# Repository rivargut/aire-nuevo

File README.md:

# aire-nuevo
Code for Aire Nuevo FW

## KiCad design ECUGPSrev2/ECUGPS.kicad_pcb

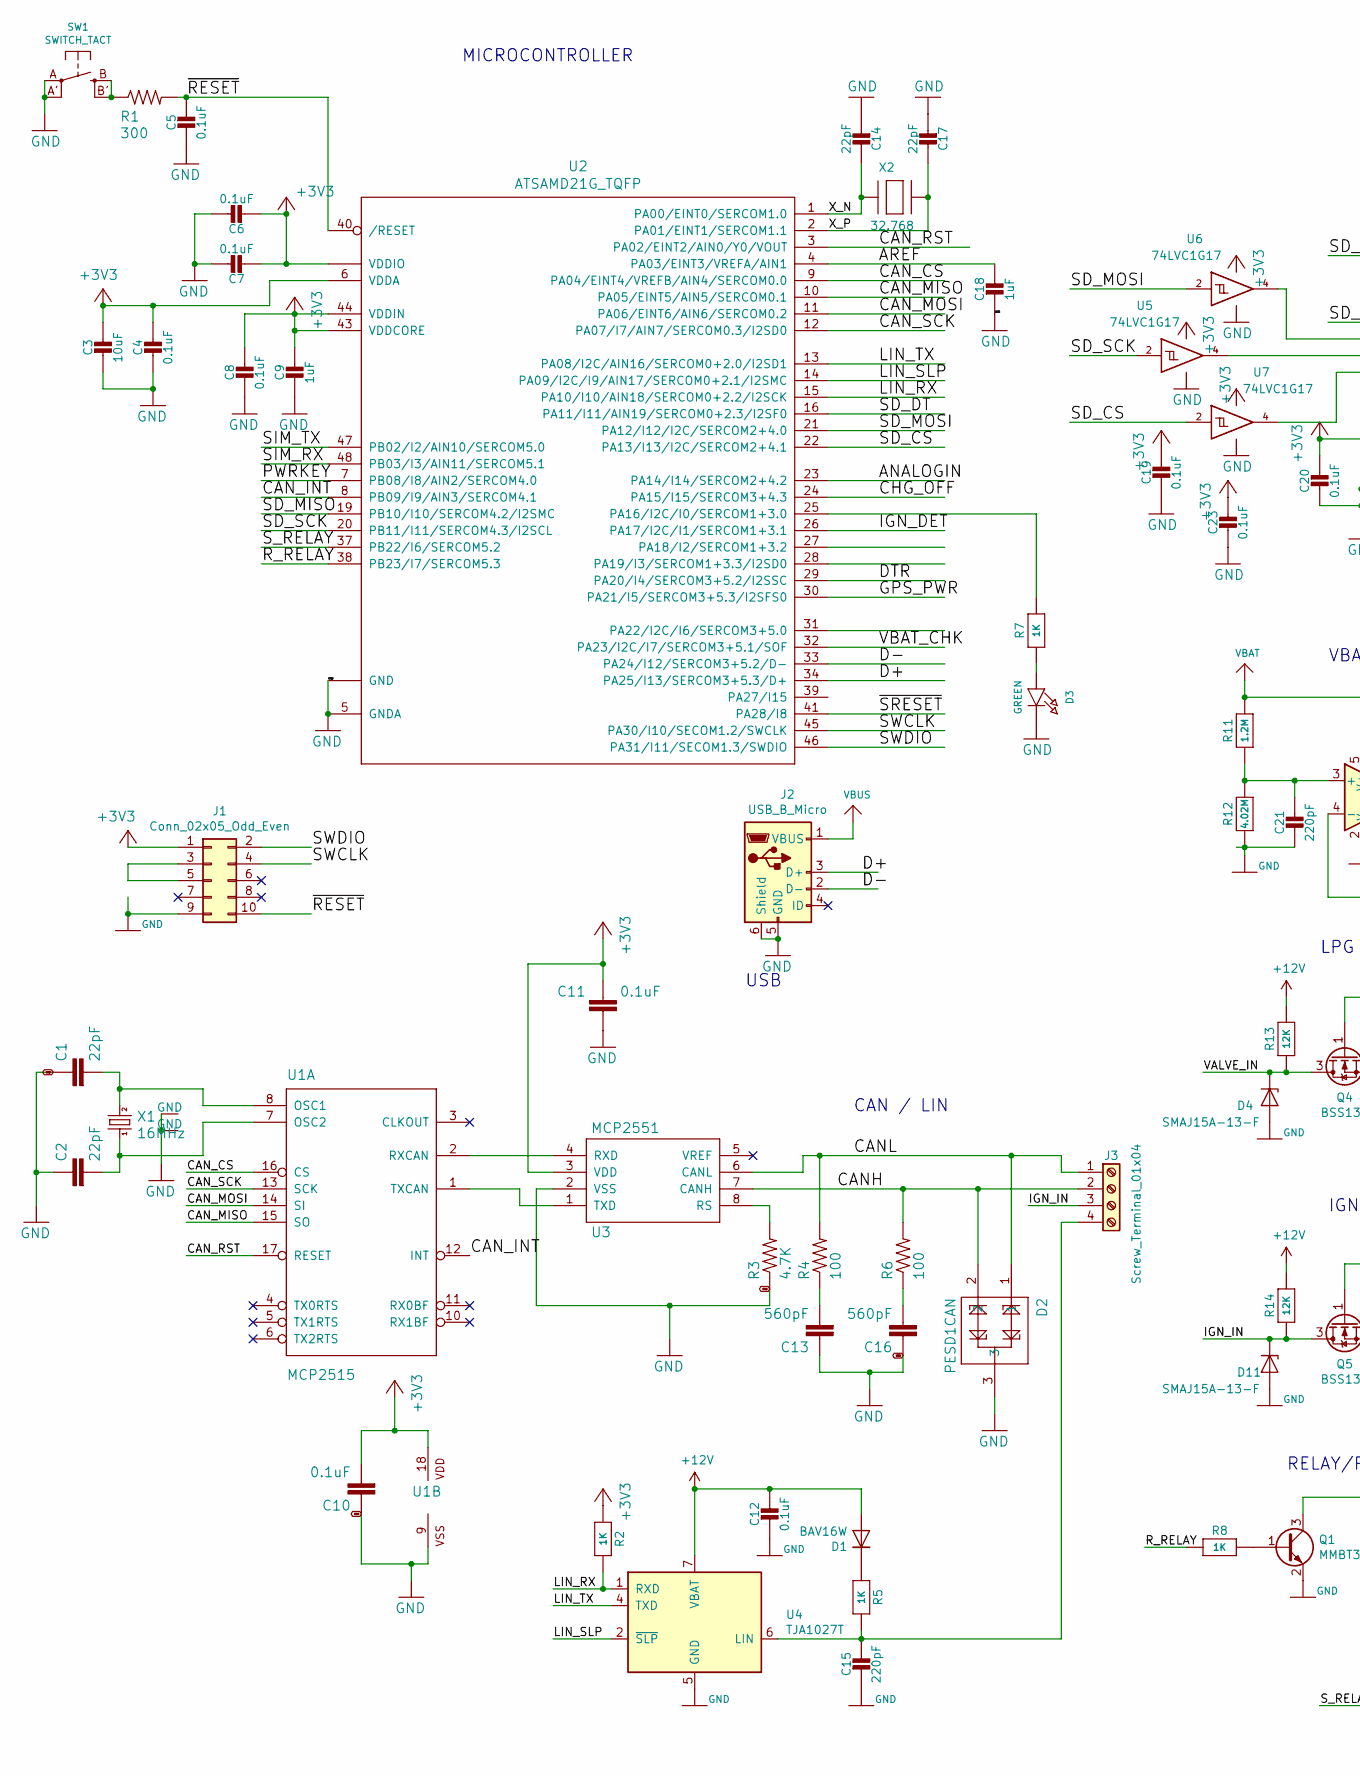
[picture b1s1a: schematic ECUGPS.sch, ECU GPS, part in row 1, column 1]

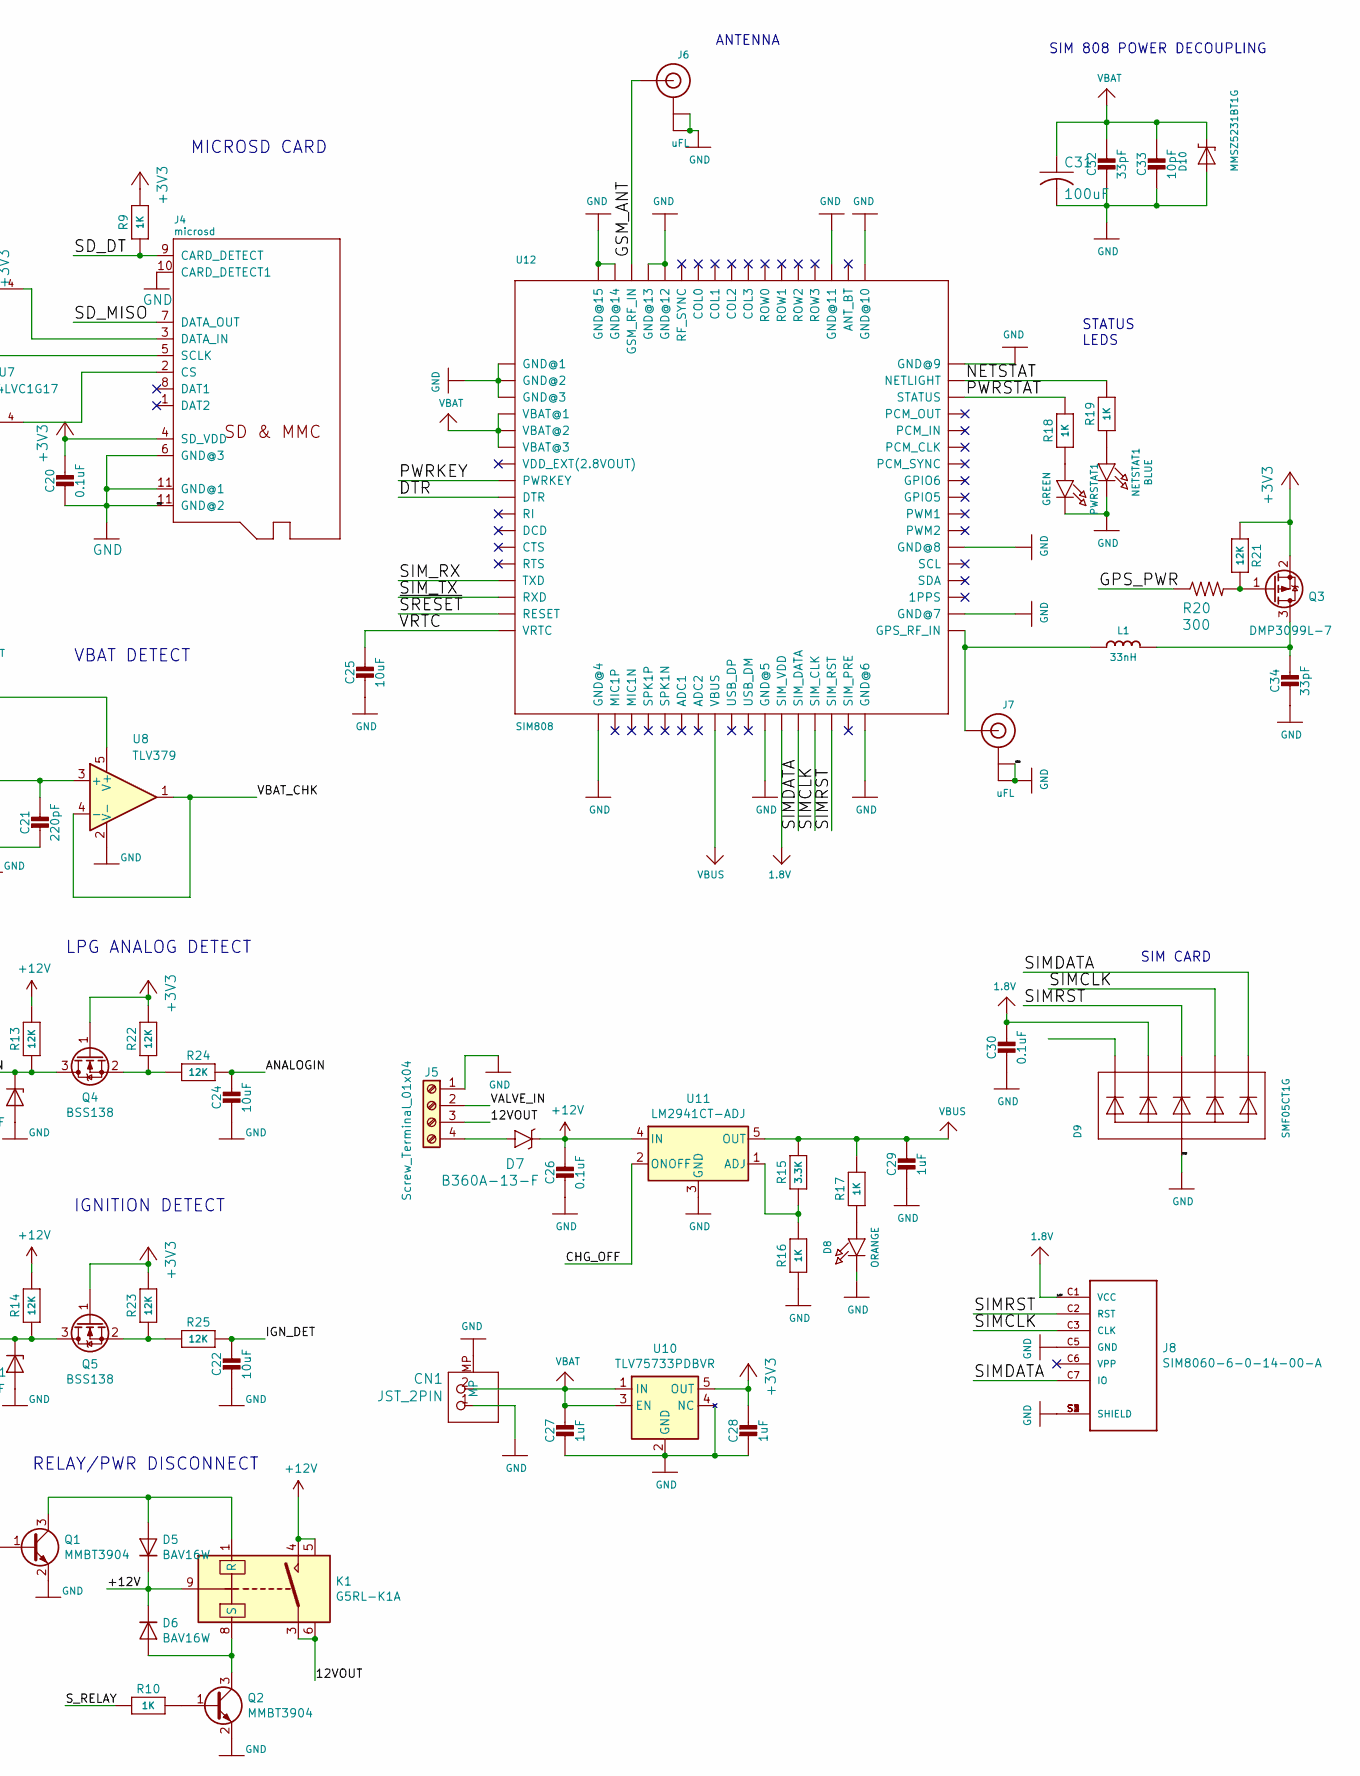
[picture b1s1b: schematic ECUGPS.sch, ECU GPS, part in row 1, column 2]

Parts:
C1, C2, C14, C17: 22pF; C_0603_1608Metric; Part CC0603JRNPO9BN220
C3, C22, C24, C25: 10uF; C_0603_1608Metric; Part 0603ZD106KAT2A
C4, C5, C6, C7, C8, C10, C11, C12, C19, C20, C23, C26, C30: 0.1uF; C_0603_1608Metric; Part CL10B104KB8NNNL
C9, C18, C27, C28, C29: 1uF; C_0603_1608Metric; Part CL10A105KP8NNNC
C13, C16: 560pF; C_0603_1608Metric; Part CL10B561KB8NNNC
C15, C21: 220pF; C_0603_1608Metric; Part CL10B221KB8NNNC
C31: 100uF; C_1206_3216Metric; Part CL31A107MQHNNNE
C32, C34: 33pF; C_0603_1608Metric; Part CL10C330JB8NNNC
C33: 10pF; C_0603_1608Metric; Part CL10C100JB8NNNC
CN1: JST_2PIN; JST_PH_S2B-PH-SM4-TB_1x02-1MP_P2.00mm_Horizontal
D1, D5, D6: BAV16W; D_SOD-123; Part BAV16W-7-F
D2: PESD1CAN; SOT-23; Part PESD1CAN-UX
D3: GREEN; LED_0805_2012Metric; Part 150080VS75000
D4, D11: SMAJ15A-13-F; D_SMA
D7: B360A-13-F‎; D_SMA; Part B360A-13-F‎
D8: ORANGE; LED_0805_2012Metric; Part LTST-C170KFKT
D9: SMF05CT1G; SOT-363_SC-70-6; Part SMF05CT1G
D10: MMSZ5231BT1G; D_SOD-123; Part MSZ5231BT1G
J1: Conn_02x05_Odd_Even; PinHeader_2x5_P1.27mm; Part 20021121-00010C4LF
J2: USB_B_Micro; GCT_USB3145-XX-X_REVB; Part 1050170001
J3, J5: Screw_Terminal_01x04; TerminalBlock_Phoenix_MPT-0,5-4-2.54_1x04_P2.54mm_Horizontal; Part OSTVN04A150
J4: microsd; Hirose_DM3D-SF; Part M3D-SF(41)
J6, J7: uFL; U.FL_Molex_MCRF_73412-0110_Vertical; Part 0734120110
J8: SIM8060-6-0-14-00-A; GCT_SIM8060-6-0-14-00-A
K1: G5RL-K1A; Relay_SPST_Omron_G5RL; Part G5RL-K1A-E-DC12
L1: 33nH; L_0805; Part CE201210-33NJ
NETSTAT1: BLUE; LED_0805_2012Metric; Part 150080BS75000
PWRSTAT1: GREEN; LED_0805_2012Metric; Part 150080VS75000
Q1, Q2: MMBT3904; SOT-23; Part MMBT3904
Q3: DMP3099L-7; SOT-23
Q4, Q5: BSS138; SOT-23
R1, R20: 300; R_0805_2012Metric; Part ERJ-6GEYJ301V
R2, R5, R7, R8, R9, R10, R16, R17, R18, R19: 1K; R_0805_2012Metric; Part ERJ-6ENF1001V
R3: 4.7K; R_0805_2012Metric; Part ERJ-6ENF4701V
R4, R6: 100; R_0805_2012Metric; Part ERJ-6ENF1000V
R11: 1.2M; R_0805_2012Metric; Part ERJ-6ENF1204V
R12: 4.02M; R_0805_2012Metric; Part RC0805FR-074M02L
R13, R14, R21, R22, R23, R24, R25: 12K; R_0805_2012Metric; Part ERJ-6ENF1202V
R15: 3.3K; R_0805_2012Metric; Part ERJ-6ENF3301V
SW1: SWITCH_TACT; EVQ-Q2; Part EVQ-Q2B03W
U1: MCP2515; SOIC-18W_7.5x11.6mm_Pitch1.27mm; Part MCP2515T-I/SO
U2: ATSAMD21G_TQFP; TQFP-48_7x7mm_P0.5mm
U3: MCP2551; SOIC-8_3.9x4.9mm_P1.27mm; Part MCP2551T-I/SN
U4: TJA1027T; SOIC-8_3.9x4.9mm_P1.27mm; Part TJA1027T/20
U5, U6, U7: 74LVC1G17; SOT-23-5
U8: TLV379; TSOP-5_1.65x3.05mm_P0.95mm
U10: TLV75733PDBVR; SOT-23-5; Part TLV75733PDBVR
U11: LM2941CT-ADJ; TO-220-5_Vertical
U12: SIM808; SIM900_SMT; Part SIM808
X1: 16MHz; Crystal_SMD_Abracon_ABM3B-4Pin_5.0x3.2mm; Part ABM3B-16.000MHZ-B2-T
X2: 32.768; Crystal_SMD_G8-2pin_3.2x1.5mm; Part FC-135 32.7680KA-A5

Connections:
1.8V: C30.1, D9.3 (C2), J8.C1 (VCC), U12.P$29 (SIM_VDD)
+3V3: C3.1, C4.1, C6.2, C7.2, C8.1, C9.1, C10.2, C11.2, C19.1, C20.1, C23.1, C28.1, J1.1, J4.4 (SD_VDD), Q3.2 (S), Q4.1 (G), Q5.1 (G), R2.2, R9.2, R21.2, R22.1, R23.1, U1.18 (VDD), U2.6 (VDDA), U2.17 (VDDIO), U2.36 (VDDIO), U2.43 (VDDCORE), U2.44 (VDDIN), U3.3 (VDD), U5.5 (VCC), U6.5 (VCC), U7.5 (VCC), U10.5 (OUT)
+12V: C12.1, C26.1, D1.2 (A), D5.1 (K), D6.1 (K), D7.1, K1.4, K1.5, K1.9, R13.1, R14.1, U4.7 (VBAT), U11.4 (IN)
/12VOUT: J5.3, K1.3, K1.6
/ANALOGIN: C24.1, R24.1, U2.23 (PA14/I14/SERCOM2+4.2)
/AREF: C18.1, U2.4 (PA03/EINT3/VREFA/AIN1)
/CANH: D2.2, J3.2, R6.2, U3.7 (CANH)
/CANL: D2.1, J3.1, R4.2, U3.6 (CANL)
/CAN_CS: U1.16 (CS), U2.9 (PA04/EINT4/VREFB/AIN4/SERCOM0.0)
/CAN_INT: U1.12 (INT), U2.8 (PB09/I9/AIN3/SERCOM4.1)
/CAN_MISO: U1.15 (SO), U2.10 (PA05/EINT5/AIN5/SERCOM0.1)
/CAN_MOSI: U1.14 (SI), U2.11 (PA06/EINT6/AIN6/SERCOM0.2)
/CAN_RST: U1.17 (RESET), U2.3 (PA02/EINT2/AIN0/Y0/VOUT)
/CAN_SCK: U1.13 (SCK), U2.12 (PA07/I7/AIN7/SERCOM0.3/I2SD0)
/CHG_OFF: U2.24 (PA15/I15/SERCOM3+4.3), U11.2 (ONOFF)
/D+: J2.3 (D+), U2.34 (PA25/I13/SERCOM3+5.3/D+)
/D-: J2.2 (D-), U2.33 (PA24/I12/SERCOM3+5.2/D-)
/DTR: U2.29 (PA20/I4/SERCOM3+5.2/I2SSC), U12.P$9 (DTR)
/GPS_PWR: R20.1, U2.30 (PA21/I5/SERCOM3+5.3/I2SFS0)
/GSM_ANT: J6.1 (SIGNAL), U12.P$66 (GSM_RF_IN)
/IGN_DET: C22.1, R25.1, U2.26 (PA17/I2C/I1/SERCOM1+3.1)
/IGN_IN: D11.1 (K), J3.3, Q5.3 (D), R14.2
/LIN_RX: R2.1, U2.15 (PA10/I10/AIN18/SERCOM0+2.2/I2SCK), U4.1 (RXD)
/LIN_SLP: U2.14 (PA09/I2C/I9/AIN17/SERCOM0+2.1/I2SMC), U4.2 (~SLP~)
/LIN_TX: U2.13 (PA08/I2C/AIN16/SERCOM0+2.0/I2SD1), U4.4 (TXD)
/NETSTAT: R19.2, U12.P$50 (NETLIGHT)
/PWRKEY: U2.7 (PB08/I8/AIN2/SERCOM4.0), U12.P$8 (PWRKEY)
/PWRSTAT: R18.2, U12.P$49 (STATUS)
/R_RELAY: R8.2, U2.38 (PB23/I7/SERCOM5.3)
/SD_CS: U2.22 (PA13/I13/I2C/SERCOM2+4.1), U7.2
/SD_DT: J4.9 (CARD_DETECT), R9.1, U2.16 (PA11/I11/AIN19/SERCOM0+2.3/I2SF0)
/SD_MISO: J4.7 (DATA_OUT), U2.19 (PB10/I10/SERCOM4.2/I2SMC)
/SD_MOSI: U2.21 (PA12/I12/I2C/SERCOM2+4.0), U6.2
/SD_SCK: U2.20 (PB11/I11/SERCOM4.3/I2SCL), U5.2
/SIMCLK: D9.5 (C4), J8.C3 (CLK), U12.P$31 (SIM_CLK)
/SIMDATA: D9.6 (C5), J8.C7 (IO), U12.P$30 (SIM_DATA)
/SIMRST: D9.4 (C3), J8.C2 (RST), U12.P$32 (SIM_RST)
/SIM_RX: U2.48 (PB03/I3/AIN11/SERCOM5.1), U12.P$14 (TXD)
/SIM_TX: U2.47 (PB02/I2/AIN10/SERCOM5.0), U12.P$15 (RXD)
/SWCLK: J1.4, U2.45 (PA30/I10/SECOM1.2/SWCLK)
/SWDIO: J1.2, U2.46 (PA31/I11/SECOM1.3/SWDIO)
/S_RELAY: R10.2, U2.37 (PB22/I6/SERCOM5.2)
/VALVE_IN: D4.1 (K), J5.2, Q4.3 (D), R13.2
/VBAT_CHK: U2.32 (PA23/I2C/I7/SERCOM3+5.1/SOF), U8.1, U8.4 (-)
/VRTC: C25.1, U12.P$17 (VRTC)
/X_N: C14.1, U2.1 (PA00/EINT0/SERCOM1.0), X2.1
/X_P: C17.1, U2.2 (PA01/EINT1/SERCOM1.1), X2.2
/~RESET: C5.1, J1.10, R1.2, U2.40 (/RESET)
/~SRESET: U2.41 (PA28/I8), U12.P$16 (RESET)
GND: C1.1, C2.1, C3.2, C4.2, C5.2, C6.1, C7.1, C8.2, C9.2, C10.1, C11.1, C12.2, C13.1, C14.2, C15.2, C16.1, C17.2, C18.2, C19.2, C20.2, C21.2, C22.2, C23.2, C24.2, C25.2, C26.2, C27.2, C28.2, C29.2, C30.2, C31.2, C32.2, C33.2, C34.2, CN1.1, CN1.MP, D2.3, D3.1 (C), D4.2 (A), D8.1 (C), D9.2 (A), D10.2, D11.2 (A), J1.9, J2.5 (GND), J2.6 (Shield), J4.6 (GND@3), J4.10 (CARD_DETECT1), J4.11 (GND@1), J5.1, J6.2 (GND@0), J7.2 (GND@0), J8.C5 (GND), J8.S1 (SHIELD), J8.S2 (SHIELD), J8.S3 (SHIELD), J8.S4 (SHIELD), NETSTAT1.1 (C), PWRSTAT1.1 (C), Q1.2 (E), Q2.2 (E), R3.1, R12.2, R16.1, SW1.A, SW1.A' (P1), U1.9 (VSS), U2.5 (GNDA), U2.18 (GND), U2.35 (GND), U2.42 (GND), U3.2 (VSS), U4.5 (GND), U5.3 (GND), U6.3 (GND), U7.3 (GND), U8.2 (V-), U10.2 (GND), U10.4 (NC), U11.3 (GND), U12.P$1 (GND@1), U12.P$2 (GND@2), U12.P$3 (GND@3), U12.P$18 (GND@4), U12.P$28 (GND@5), U12.P$34 (GND@6), U12.P$36 (GND@7), U12.P$40 (GND@8), U12.P$51 (GND@9), U12.P$52 (GND@10), U12.P$54 (GND@11), U12.P$64 (GND@12), U12.P$65 (GND@13), U12.P$67 (GND@14), U12.P$68 (GND@15), X1.2 (GND), X1.4 (GND)
unnamed: C1.2, U1.8 (OSC1), X1.3 (2)
unnamed: C2.2, U1.7 (OSC2), X1.1
unnamed: C13.2, R4.1
unnamed: C15.1, J3.4, R5.1, U4.6 (LIN)
unnamed: C16.2, R6.1
unnamed: C21.1, R11.2, R12.1, U8.3 (+)
unnamed: C34.1, L1.2, Q3.3 (D)
unnamed: D1.1 (K), R5.2
unnamed: D3.2 (A), R7.1
unnamed: D5.2 (A), K1.1 (R), Q1.3 (C)
unnamed: D6.2 (A), K1.8 (S), Q2.3 (C)
unnamed: D7.2, J5.4
unnamed: D8.2 (A), R17.1
unnamed: J1.3, J1.5
unnamed: J4.2 (CS), U7.4
unnamed: J4.3 (DATA_IN), U6.4
unnamed: J4.5 (SCLK), U5.4
unnamed: J7.1 (SIGNAL), L1.1, U12.P$35 (GPS_RF_IN)
unnamed: NETSTAT1.2 (A), R19.1
unnamed: PWRSTAT1.2 (A), R18.1
unnamed: Q1.1 (B), R8.1
unnamed: Q2.1 (B), R10.1
unnamed: Q3.1 (G), R20.2, R21.1
unnamed: Q4.2 (S), R22.2, R24.2
unnamed: Q5.2 (S), R23.2, R25.2
unnamed: R1.1, SW1.B (S), SW1.B' (S1)
unnamed: R3.2, U3.8 (RS)
unnamed: R7.2, U2.25 (PA16/I2C/I0/SERCOM1+3.0)
unnamed: R15.2, R16.2, U11.1 (ADJ)
unnamed: U1.1 (TXCAN), U3.1 (TXD)
unnamed: U1.2 (RXCAN), U3.4 (RXD)
VBAT: C27.1, C31.1, C32.1, C33.1, CN1.2, D10.1, R11.1, U8.5 (V+), U10.1 (IN), U10.3 (EN), U12.P$4 (VBAT@1), U12.P$5 (VBAT@2), U12.P$6 (VBAT@3)
VBUS: C29.1, J2.1 (VBUS), R15.1, R17.2, U11.5 (OUT), U12.P$25 (VBUS)

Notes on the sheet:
ANTENNA
SIM 808 POWER DECOUPLING
SIM CARD
STATUS LEDS
MICROCONTROLLER
MICROSD CARD
USB
CAN / LIN
LPG ANALOG DETECT
RELAY/PWR DISCONNECT
VBAT DETECT
IGNITION DETECT

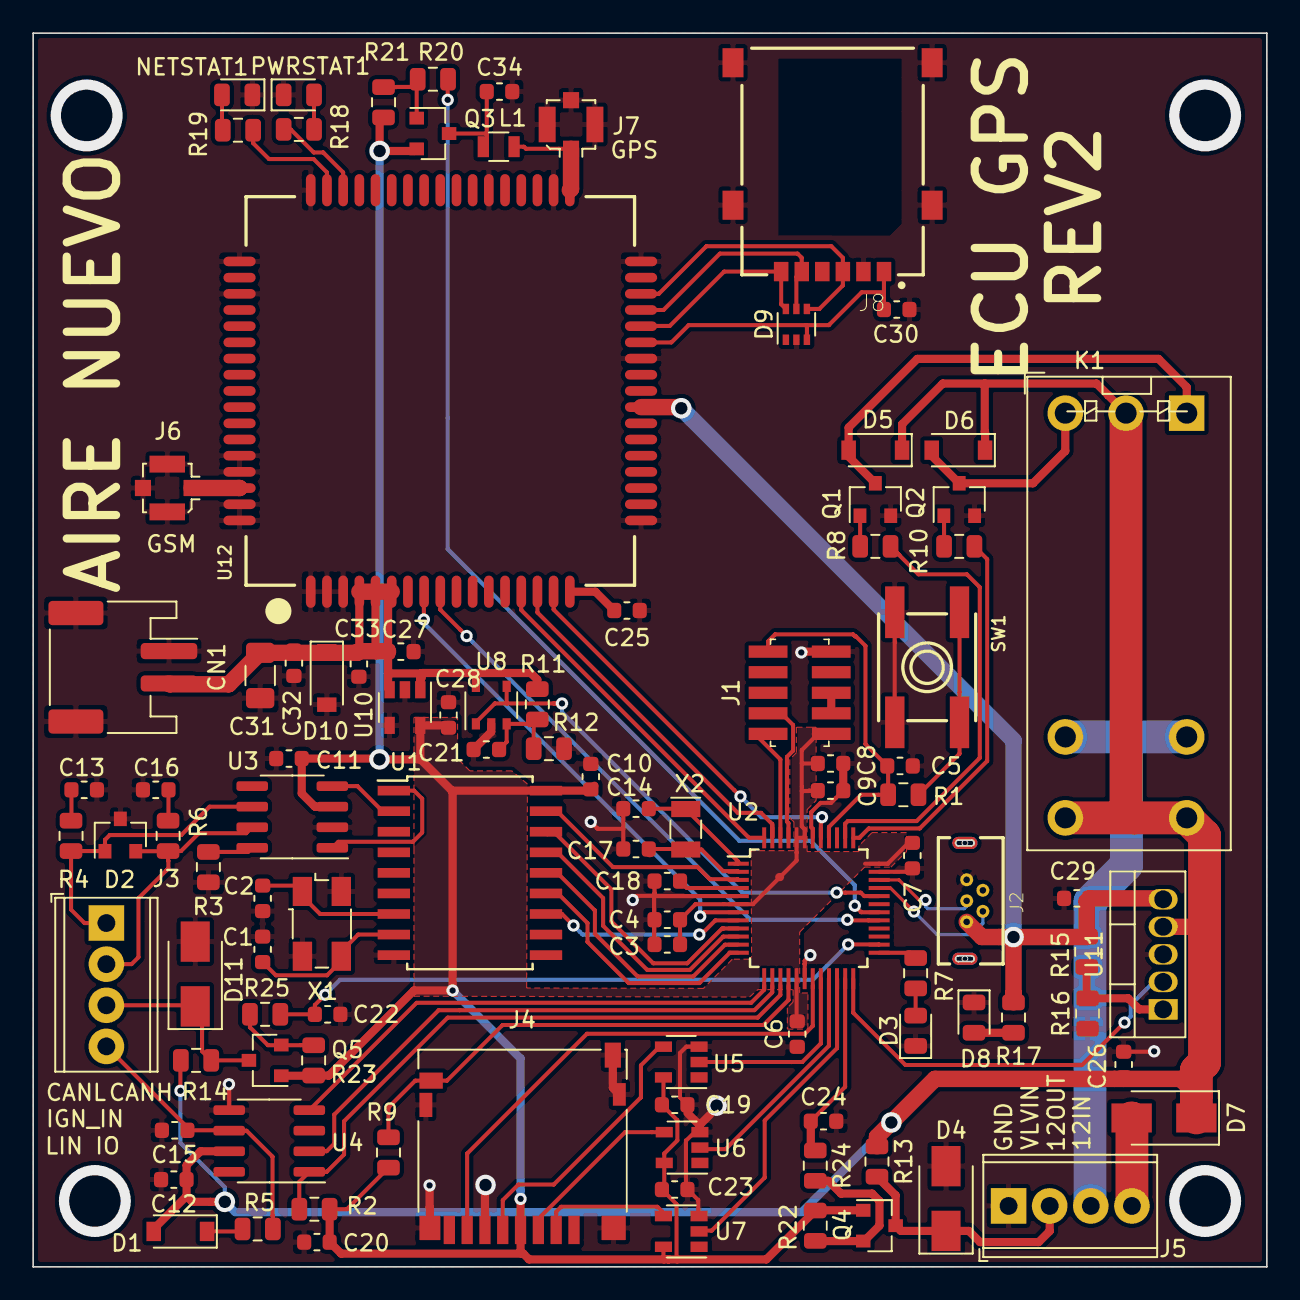
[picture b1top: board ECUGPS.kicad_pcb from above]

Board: 2 copper layers, 76.2 x 76.2 mm, 102 parts (0 on the bottom side), 83 nets.

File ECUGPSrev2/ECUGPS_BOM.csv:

"Id";"Designator";"Package";"Quantity";"Designation";"Supplier and ref";
1;"J8";"GCT_SIM8060-6-0-14-00-A";1;"SIM8060-6-0-14-00-A";;;
2;"C23,C30,C19,C20,C4,C6,C26,C12,C11,C10,C5,C8,C7";"C_0603_1608Metric";13;"0.1uF";;;
3;"C21,C15";"C_0603_1608Metric";2;"220pF";;;
4;"CN1";"JST_PH_S2B-PH-SM4-TB_1x02-1MP_P2.00mm_Horizontal";1;"JST_2PIN";;;
5;"D9";"SOT-363_SC-70-6";1;"SMF05CT1G";;;
6;"R13,R25,R24,R23,R22,R14,R21";"R_0805_2012Metric";7;"12K";;;
7;"D2";"SOT-23";1;"PESD1CAN";;;
8;"X1";"Crystal_SMD_Abracon_ABM3B-4Pin_5.0x3.2mm";1;"16MHz";;;
9;"U3";"SOIC-8_3.9x4.9mm_P1.27mm";1;"MCP2551";;;
10;"Q5,Q4";"SOT-23";2;"BSS138";;;
11;"J5,J3";"TerminalBlock_Phoenix_MPT-0,5-4-2.54_1x04_P2.54mm_Horizontal";2;"Screw_Terminal_01x04";;;
12;"D11,D4";"D_SMA";2;"SMAJ15A-13-F";;;
13;"C22,C3,C25,C24";"C_0603_1608Metric";4;"10uF";;;
14;"U11";"TO-220-5_Vertical";1;"LM2941CT-ADJ";;;
15;"U8";"TSOP-5_1.65x3.05mm_P0.95mm";1;"TLV379";;;
16;"R16,R17,R5,R2,R19,R18,R7,R10,R8,R9";"R_0805_2012Metric";10;"1K";;;
17;"R15";"R_0805_2012Metric";1;"3.3K";;;
18;"R12";"R_0805_2012Metric";1;"4.02M";;;
19;"R11";"R_0805_2012Metric";1;"1.2M";;;
20;"C31";"C_1206_3216Metric";1;"100uF";;;
21;"C34,C32";"C_0603_1608Metric";2;"33pF";;;
22;"U12";"SIM900_SMT";1;"SIM808";;;
23;"J2";"GCT_USB3145-XX-X_REVB";1;"USB_B_Micro";;;
24;"U7,U6,U5";"SOT-23-5";3;"74LVC1G17";;;
25;"U2";"TQFP-48_7x7mm_P0.5mm";1;"ATSAMD21G_TQFP";;;
26;"U10";"SOT-23-5";1;"TLV75733PDBVR";;;
27;"U4";"SOIC-8_3.9x4.9mm_P1.27mm";1;"TJA1027T";;;
28;"R20,R1";"R_0805_2012Metric";2;"300";;;
29;"Q3";"SOT-23";1;" DMP3099L-7  ";;;
30;"D1,D6,D5";"D_SOD-123";3;"BAV16W";;;
31;"C28,C29,C27,C18,C9";"C_0603_1608Metric";5;"1uF";;;
32;"C17,C14,C2,C1";"C_0603_1608Metric";4;"22pF";;;
33;"K1";"Relay_SPST_Omron_G5RL";1;"G5RL-K1A";;;
34;"J6,J7";"U.FL_Molex_MCRF_73412-0110_Vertical";2;"uFL";;;
35;"L1";"L_0805";1;"33nH";;;
36;"C16,C13";"C_0603_1608Metric";2;"560pF";;;
37;"R6,R4";"R_0805_2012Metric";2;"100";;;
38;"R3";"R_0805_2012Metric";1;"4.7K";;;
39;"PWRSTAT1,D3";"LED_0805_2012Metric";2;"GREEN";;;
40;"NETSTAT1";"LED_0805_2012Metric";1;"BLUE";;;
41;"D10";"D_SOD-123";1;"MMSZ5231BT1G";;;
42;"D7";"D_SMA";1;"B360A-13-F‎";;;
43;"D8";"LED_0805_2012Metric";1;"ORANGE";;;
44;"C33";"C_0603_1608Metric";1;"10pF";;;
45;"J4";"Hirose_DM3D-SF";1;"microsd";;;
46;"Q2,Q1";"SOT-23";2;"MMBT3904";;;
47;"X2";"Crystal_SMD_G8-2pin_3.2x1.5mm";1;"32.768";;;
48;"U1";"SOIC-18W_7.5x11.6mm_Pitch1.27mm";1;"MCP2515";;;
49;"SW1";"EVQ-Q2";1;"SWITCH_TACT";;;
50;"J1";"PinHeader_2x5_P1.27mm";1;"Conn_02x05_Odd_Even";;;

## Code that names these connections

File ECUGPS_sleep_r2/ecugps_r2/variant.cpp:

/*
  Copyright (c) 2014-2015 Arduino LLC.  All right reserved.

  This library is free software; you can redistribute it and/or
  modify it under the terms of the GNU Lesser General Public
  License as published by the Free Software Foundation; either
  version 2.1 of the License, or (at your option) any later version.

  This library is distributed in the hope that it will be useful,
  but WITHOUT ANY WARRANTY; without even the implied warranty of
  MERCHANTABILITY or FITNESS FOR A PARTICULAR PURPOSE.
  See the GNU Lesser General Public License for more details.

  You should have received a copy of the GNU Lesser General Public
  License along with this library; if not, write to the Free Software
  Foundation, Inc., 51 Franklin St, Fifth Floor, Boston, MA  02110-1301  USA
*/


// Ricardo Vargas 14 June 2020
// ECU GPS rev 2 board
#include "variant.h"

/*
 * Pins descriptions
 */
const PinDescription g_APinDescription[]=
{

  // 0 - LPG Valve detect - rev1 used analog, rev 2 uses digital channel
  { PORTA, 14, PIO_DIGITAL, PIN_ATTR_DIGITAL, No_ADC_Channel, NOT_ON_PWM, NOT_ON_TIMER, EXTERNAL_INT_11 }, // ANALOG IN
  // 1..3 - LIN Controller
  { PORTA,  8, PIO_SERCOM_ALT, PIN_ATTR_NONE, No_ADC_Channel, NOT_ON_PWM, NOT_ON_TIMER, EXTERNAL_INT_10 }, // LIN TX
  { PORTA, 10, PIO_SERCOM_ALT, PIN_ATTR_NONE, No_ADC_Channel, NOT_ON_PWM, NOT_ON_TIMER, EXTERNAL_INT_9 }, // LIN RX
  { PORTA,  9, PIO_DIGITAL, PIN_ATTR_DIGITAL, No_ADC_Channel, NOT_ON_PWM, NOT_ON_TIMER, EXTERNAL_INT_8 },  // LIN_SLP  


  // 4..7 - SIM IO pins
  // --------------------

  { PORTA, 28, PIO_DIGITAL, PIN_ATTR_DIGITAL, No_ADC_Channel, NOT_ON_PWM, NOT_ON_TIMER, EXTERNAL_INT_NONE }, // SIM RESET
  { PORTB,  2, PIO_SERCOM_ALT, PIN_ATTR_NONE, No_ADC_Channel, NOT_ON_PWM, NOT_ON_TIMER, EXTERNAL_INT_2 }, // SIM TX
  { PORTB,  3, PIO_SERCOM_ALT, PIN_ATTR_NONE, No_ADC_Channel, NOT_ON_PWM, NOT_ON_TIMER, EXTERNAL_INT_3 }, // SIM RX
  { PORTB,  7, PIO_DIGITAL, PIN_ATTR_DIGITAL, No_ADC_Channel, NOT_ON_PWM, NOT_ON_TIMER, EXTERNAL_INT_NONE  }, // SIM PWR KEY

  // 8..9 I2C pins (SDA/SCL and also EDBG:SDA/SCL)
  // ----------------------
  { PORTA, 22, PIO_SERCOM, PIN_ATTR_DIGITAL, No_ADC_Channel, NOT_ON_PWM, NOT_ON_TIMER, EXTERNAL_INT_6 }, // SDA: SERCOM3/PAD[0]
  { PORTA, 23, PIO_SERCOM, PIN_ATTR_DIGITAL, No_ADC_Channel, NOT_ON_PWM, NOT_ON_TIMER, EXTERNAL_INT_7 }, // SCL: SERCOM3/PAD[1]

  // 10..14 - SD SPI pins (ICSP:MISO,SCK,MOSI), IO
  // ----------------------
  { PORTA, 12, PIO_SERCOM_ALT, PIN_ATTR_DIGITAL, No_ADC_Channel, NOT_ON_PWM, NOT_ON_TIMER, EXTERNAL_INT_12 }, // SD MOSI: SERCOM4/PAD[0]
  { PORTB, 10, PIO_SERCOM_ALT, PIN_ATTR_DIGITAL, No_ADC_Channel, NOT_ON_PWM, NOT_ON_TIMER, EXTERNAL_INT_10 }, // SD MISO: SERCOM4/PAD[2]
  { PORTB, 11, PIO_SERCOM_ALT, PIN_ATTR_DIGITAL, No_ADC_Channel, NOT_ON_PWM, NOT_ON_TIMER, EXTERNAL_INT_11 }, // SD SCK: SERCOM4/PAD[3]
  { PORTA, 13, PIO_SERCOM_ALT, PIN_ATTR_DIGITAL, No_ADC_Channel, NOT_ON_PWM, NOT_ON_TIMER, EXTERNAL_INT_13 },    // SD CS: SERCOM4/PAD[1]
  { PORTA, 11, PIO_DIGITAL, PIN_ATTR_DIGITAL, No_ADC_Channel, NOT_ON_PWM, NOT_ON_TIMER, EXTERNAL_INT_14 },  // SD DT
  

  // 15..16 - USB
  // --------------------
  { PORTA, 24, PIO_COM, PIN_ATTR_NONE, No_ADC_Channel, NOT_ON_PWM, NOT_ON_TIMER, EXTERNAL_INT_NONE }, // USB/DM
  { PORTA, 25, PIO_COM, PIN_ATTR_NONE, No_ADC_Channel, NOT_ON_PWM, NOT_ON_TIMER, EXTERNAL_INT_NONE }, // USB/DP


  // 17/18 I2C (SDA/SCL and also EDBG:SDA/SCL)
  { PORTA, 22, PIO_SERCOM, PIN_ATTR_NONE, No_ADC_Channel, NOT_ON_PWM, NOT_ON_TIMER, EXTERNAL_INT_NONE }, // SDA: SERCOM3/PAD[0]
  { PORTA, 23, PIO_SERCOM, PIN_ATTR_NONE, No_ADC_Channel, NOT_ON_PWM, NOT_ON_TIMER, EXTERNAL_INT_NONE }, // SCL: SERCOM3/PAD[1]

  // 19..24 - CAN Controller
  { PORTA,  2, PIO_DIGITAL, PIN_ATTR_DIGITAL, No_ADC_Channel, NOT_ON_PWM, NOT_ON_TIMER, EXTERNAL_INT_2 }, // CAN_RST
  { PORTB,  9, PIO_DIGITAL, PIN_ATTR_DIGITAL, No_ADC_Channel, NOT_ON_PWM, NOT_ON_TIMER, EXTERNAL_INT_9 }, // CAN_INT
  { PORTA, 5, PIO_SERCOM, PIN_ATTR_NONE, No_ADC_Channel, NOT_ON_PWM, NOT_ON_TIMER, EXTERNAL_INT_NONE }, // CAN MISO: SERCOM1/PAD[3]
  { PORTA, 6, PIO_SERCOM, PIN_ATTR_NONE, No_ADC_Channel, NOT_ON_PWM, NOT_ON_TIMER, EXTERNAL_INT_NONE }, // CAN MOSI: SERCOM1/PAD[0]
  { PORTA, 7, PIO_SERCOM, PIN_ATTR_NONE, No_ADC_Channel, NOT_ON_PWM, NOT_ON_TIMER, EXTERNAL_INT_NONE }, // CAN SCK: SERCOM1/PAD[1]
  { PORTA, 4, PIO_SERCOM, PIN_ATTR_NONE, No_ADC_Channel, NOT_ON_PWM, NOT_ON_TIMER, EXTERNAL_INT_NONE }, // CAN SS: SERCOM1/PAD[2]

  // 25..26 Reset/Set Relay
  { PORTB,  22, PIO_DIGITAL, PIN_ATTR_DIGITAL, No_ADC_Channel, NOT_ON_PWM, NOT_ON_TIMER, EXTERNAL_INT_NONE }, // R_RELAY
  { PORTB,  23, PIO_DIGITAL, PIN_ATTR_DIGITAL, No_ADC_Channel, NOT_ON_PWM, NOT_ON_TIMER, EXTERNAL_INT_NONE }, // S_RELAY

  // 27 (AREF)
  { PORTA, 3, PIO_ANALOG, PIN_ATTR_ANALOG, No_ADC_Channel, NOT_ON_PWM, NOT_ON_TIMER, EXTERNAL_INT_NONE }, // DAC/VREFP

  // 28..31 New digital functions
  { PORTA, 17, PIO_DIGITAL, PIN_ATTR_DIGITAL, No_ADC_Channel, NOT_ON_PWM, NOT_ON_TIMER, EXTERNAL_INT_1 }, // IGN_DET
  { PORTA, 20, PIO_DIGITAL, PIN_ATTR_DIGITAL, No_ADC_Channel, NOT_ON_PWM, NOT_ON_TIMER, EXTERNAL_INT_4 }, // DTR (SIMCOM module)
  { PORTA, 15, PIO_DIGITAL, PIN_ATTR_DIGITAL, No_ADC_Channel, NOT_ON_PWM, NOT_ON_TIMER, EXTERNAL_INT_15 }, // CHG_OFF  
  { PORTA, 21, PIO_DIGITAL, PIN_ATTR_DIGITAL, No_ADC_Channel, NOT_ON_PWM, NOT_ON_TIMER, EXTERNAL_INT_NONE }, // GPS_PWR

  // 31..35 Unused pins
  { PORTA, 16, PIO_TIMER, (PIN_ATTR_DIGITAL|PIN_ATTR_PWM|PIN_ATTR_TIMER), No_ADC_Channel, PWM2_CH0, TCC2_CH0, EXTERNAL_INT_0 }, // TCC2/WO[0]
  { PORTA, 18, PIO_TIMER, (PIN_ATTR_DIGITAL|PIN_ATTR_PWM|PIN_ATTR_TIMER), No_ADC_Channel, PWM3_CH0, TC3_CH0, EXTERNAL_INT_2 }, // TC3/WO[0]
  { PORTA, 19, PIO_TIMER_ALT, (PIN_ATTR_DIGITAL|PIN_ATTR_PWM|PIN_ATTR_TIMER_ALT), No_ADC_Channel, PWM0_CH3, TCC0_CH3, EXTERNAL_INT_3 }, // TCC0/WO[3]
  { PORTA, 27, PIO_OUTPUT, PIN_ATTR_DIGITAL, No_ADC_Channel, NOT_ON_PWM, NOT_ON_TIMER, EXTERNAL_INT_NONE }, // used as output only

  // ----------------------
  // 34..35 - Alternate use of A0 (DAC output), 44 SWCLK, 45, SWDIO

  { PORTA, 30, PIO_PWM, PIN_ATTR_DIGITAL|PIO_SERCOM, No_ADC_Channel, NOT_ON_PWM, TCC1_CH0, EXTERNAL_INT_10 }, // SWCLK
  { PORTA, 31, PIO_PWM, PIN_ATTR_DIGITAL|PIO_SERCOM, No_ADC_Channel, NOT_ON_PWM, TCC1_CH1, EXTERNAL_INT_11 }, // SWDIO
} ;

extern "C" {
    unsigned int PINCOUNT_fn() {
        return (sizeof(g_APinDescription) / sizeof(g_APinDescription[0]));
    }
}

const void* g_apTCInstances[TCC_INST_NUM+TC_INST_NUM]={ TCC0, TCC1, TCC2, TC3, TC4, TC5 } ;

// Multi-serial objects instantiation
SERCOM sercom0( SERCOM0 ) ;
//SERCOM sercom1( SERCOM1 ) ;
SERCOM sercom2( SERCOM2 ) ;
//SERCOM sercom3( SERCOM3 ) ;
SERCOM sercom4( SERCOM4 ) ;
SERCOM sercom5( SERCOM5 ) ;

Uart Serial1( &sercom5, PIN_SERIAL1_RX, PIN_SERIAL1_TX, PAD_SERIAL1_RX, PAD_SERIAL1_TX ) ;  // SIM UART port
Uart Serial2( &sercom2, PIN_SERIAL2_RX, PIN_SERIAL2_TX, PAD_SERIAL2_RX, PAD_SERIAL2_TX ) ; // LIN UART port

void SERCOM2_Handler()
{
  Serial2.IrqHandler();
}

void SERCOM5_Handler()
{
  Serial1.IrqHandler();
}

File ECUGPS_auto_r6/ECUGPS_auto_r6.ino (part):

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#define LPGSTATUSPIN 0 // A0  input now digital
#define ISO_TX 1
#define ISO_RX 2
#define LIN_SLP 3 // sleep pin for LIN IC


// pin for FONA
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#define FONA_PWRKEY 7

//CAN Bus
#define CAN_RST 19

// Set reset for 12V relay
#define PIN_OFF 25
#define PIN_ON 26

// Power pins
#define IGN_DET 28
#define DTR 29
#define PWR_GATE 30 
#define PWR_GPS 31

// SD pins
#define SD_CS 13
#define SD_DT 14

/// MACROS

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  pinMode(PIN_ON, OUTPUT);
  pinMode(PIN_OFF, OUTPUT);
  pinMode(FONA_RST, OUTPUT);
  pinMode(SD_CS, OUTPUT);
  pinMode(LIN_SLP,OUTPUT);
  pinMode(SD_DT,INPUT);
  pinMode(IGN_DET,INPUT);
  pinMode(DTR,OUTPUT);
  pinMode(PWR_GATE,OUTPUT);
  pinMode(PWR_GPS,OUTPUT); 
  pinMode(CAN_RST,OUTPUT);

  digitalWrite(CAN_RST,HIGH);  
  digitalWrite(LIN_SLP, HIGH);
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   wdt.attachShutdown(wdt_reset);
   wdt.setup(WDT_SOFTCYCLE8M);
   // Interrupt setup  
   LowPower.attachInterruptWakeup(digitalPinToInterrupt(IGN_DET), Ignition, CHANGE);
   startmillis = millis(); // discount setup time from delta.
   printlogln("*****  Init End  ******\r\n");
   sendText(SMSphone,"ECU-GPS booted OK");
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
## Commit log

2019-12-30 Add files via upload
    - Fixed reset on the SIM808 (pull up at start up)
    - Fixed port numbers
2019-12-30 Add files via upload
    Fixed pin definition
2020-02-12 Add files via upload
    Changes up to 12 FEB,
    included battery voltage read command through SMS
    Other changes by Daniel
2020-02-24 Add files via upload
    FONA charge mode changes
2020-02-24 Add files via upload
    changes fro charger implementation
2020-02-26 Add files via upload
    Se habilita el modo de recarga de batería. Grabándolo en EPROM y reseteando del FONA automáticamente.
2020-02-26 Add files via upload
    Se arregla el error al imprimir el porcentaje de batería antes de hacer httpost
2020-02-28 Add files via upload
    Sleep test using RTC , with changes to usb detach and attach
2020-03-01 Add files via upload
    Se agrega una función que realiza un último post del día (23:58:00)
2020-03-01 Add files via upload
    Al final de la función httppost, se intenta apagar el gprs aunque parezca que no se logró encender. Esto porque a veces queda encendido
2020-03-01 Add files via upload
    Ediciones a la función DayClosingPost(). Además la función HTTPPost() ahora es de tipo bool y retorna la variable success
2020-03-02 Add files via upload
    El relay deja de ser alimentado. Esto para ahorro de energía. Sólo se alimenta en la transición de estado, y luego se vuelve a desconectar.
